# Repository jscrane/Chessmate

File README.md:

# Commodore CHESSmate

An emulation of the [Commodore CHESSmate](https://commodore.international/2022/03/26/the-history-of-the-commodore-chessmate/)
based on information from [Hans Otten](http://retro.hansotten.nl/6502-sbc/6530-6532/chessmate/).

Inspired by an article on [Hackaday](https://hackaday.com/2023/11/14/the-quaint-history-of-the-commodore-chessmate/)!

## Software

### Common
- [6502 Emulation](https://github.com/jscrane/r65emu) library
- [Arduino IDE](https://www.arduino.cc/en/software/) or [uC-Makefile](https://github.com/jscrane/uC-Makefile)

Please [configure](https://github.com/jscrane/r65emu#configuration-for-arduino) the Emulation library for your hardware.

### ESP8266
- [ESP8266 Arduino core](https://github.com/esp8266/Arduino.git)
- [TFT_eSPI](https://github.com/Bodmer/TFT_eSPI) library

Please [configure](https://github.com/Bodmer/TFT_eSPI/blob/master/User_Setup_Select.h) TFT_eSPI for your hardware.

### ESP32
- [ESP32 Arduino core](https://github.com/espressif/arduino-esp32)
- [FabGL](https://github.com/fdivitto/FabGL)

## Hardware

### Input
- a PS/2 keyboard, or
- a serial terminal, or
- hardware pushbuttons

See `config.h`.

### ESP8266
- A board, e.g., [WeMOS](https://www.wemos.cc/en/latest/d1/d1_mini.html)
- A display supported by TFT_eSPI, e.g., ILI9341

### ESP32
- A board, e.g., [LilyGO TTGO](https://www.tinytronics.nl/shop/en/development-boards/microcontroller-boards/with-wi-fi/lilygo-ttgo-vga32-esp32)
- A custom PCB with a `node32s`, see below.

## Acknowledgement

Thanks to **PCBWay** for sponsoring this lovely PCB; their service was prompt, efficient and their [KiCad plugin](https://www.pcbway.com/blog/News/PCBWay_Plug_In_for_KiCad_3ea6219c.html) made ordering painless!

- KiCad files are [here](/kicad/)
- Software for this configuration can be built (with `uC-Makefile`) as `make t=esp32`

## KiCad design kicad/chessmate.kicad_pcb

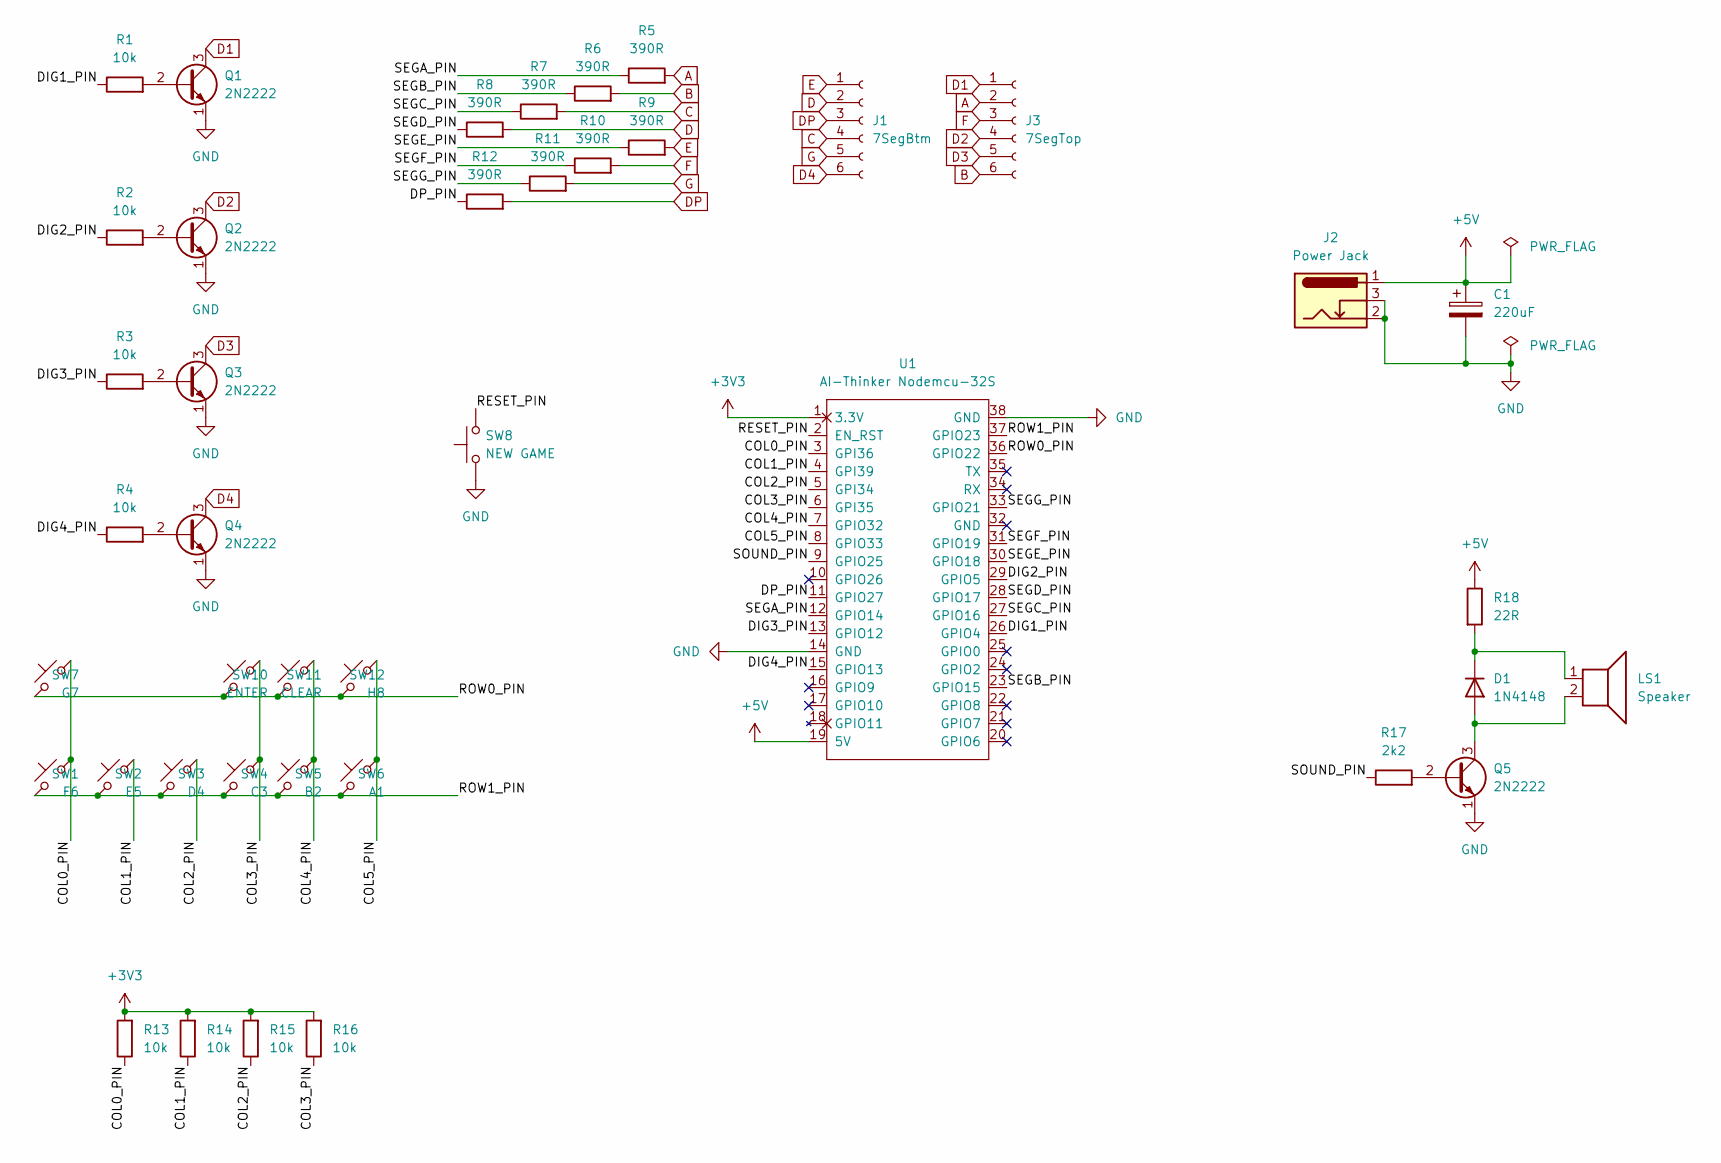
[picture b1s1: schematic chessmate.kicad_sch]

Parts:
C1: 220uF; CP_Radial_D6.3mm_P2.50mm
D1: 1N4148; D_DO-35_SOD27_P7.62mm_Horizontal
J1: 7SegBtm; PinHeader_1x06_P2.54mm_Vertical
J2: Power Jack; BarrelJack_Horizontal
J3: 7SegTop; PinHeader_1x06_P2.54mm_Vertical
LS1: Speaker; Buzzer_12x9.5RM7.0
Q1, Q2, Q3, Q4, Q5: 2N2222; TO-92_Inline
R1, R2, R3, R4: 10k; R_Axial_DIN0207_L6.3mm_D2.5mm_P2.54mm_Vertical
R5, R6, R7, R8, R9, R10, R11, R12: 390R; R_Axial_DIN0207_L6.3mm_D2.5mm_P2.54mm_Vertical
R13, R14, R15, R16: 10k; R_Axial_DIN0207_L6.3mm_D2.5mm_P7.62mm_Horizontal
R17: 2k2; R_Axial_DIN0207_L6.3mm_D2.5mm_P2.54mm_Vertical
R18: 22R; R_Axial_DIN0207_L6.3mm_D2.5mm_P2.54mm_Vertical
SW1: F6; SW_PUSH_6mm_H4.3mm
SW2: E5; SW_PUSH_6mm_H4.3mm
SW3: D4; SW_PUSH_6mm_H4.3mm
SW4: C3; SW_PUSH_6mm_H4.3mm
SW5: B2; SW_PUSH_6mm_H4.3mm
SW6: A1; SW_PUSH_6mm_H4.3mm
SW7: G7; SW_PUSH_6mm_H4.3mm
SW8: NEW GAME; SW_PUSH_6mm_H4.3mm
SW10: ENTER; SW_PUSH_6mm_H4.3mm
SW11: CLEAR; SW_PUSH_6mm_H4.3mm
SW12: H8; SW_PUSH_6mm_H4.3mm
U1: AI-Thinker Nodemcu-32S; ai-thinker nodemcu-32s

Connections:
+3V3: R13.2, R14.2, R15.2, R16.2, U1.1 (3.3V)
+5V: C1.1, J2.1, R18.1, U1.19 (5V)
/COL0_PIN: R13.1, SW1.2, SW7.2, U1.3 (GPI36)
/COL1_PIN: R14.1, SW2.2, U1.4 (GPI39)
/COL2_PIN: R15.1, SW3.2, U1.5 (GPI34)
/COL3_PIN: R16.1, SW4.2, SW10.2, U1.6 (GPI35)
/COL4_PIN: SW5.2, SW11.2, U1.7 (GPIO32)
/COL5_PIN: SW6.2, SW12.2, U1.8 (GPIO33)
/DIG1_PIN: R1.1, U1.26 (GPIO4)
/DIG2_PIN: R2.1, U1.29 (GPIO5)
/DIG3_PIN: R3.1, U1.13 (GPIO12)
/DIG4_PIN: R4.1, U1.15 (GPIO13)
/DP_PIN: R12.1, U1.11 (GPIO27)
/RESET_PIN: SW8.2, U1.2 (EN_RST)
/ROW0_PIN: SW7.1, SW10.1, SW11.1, SW12.1, U1.36 (GPIO22)
/ROW1_PIN: SW1.1, SW2.1, SW3.1, SW4.1, SW5.1, SW6.1, U1.37 (GPIO23)
/SEGA_PIN: R5.1, U1.12 (GPIO14)
/SEGB_PIN: R6.1, U1.23 (GPIO15)
/SEGC_PIN: R7.1, U1.27 (GPIO16)
/SEGD_PIN: R8.1, U1.28 (GPIO17)
/SEGE_PIN: R9.1, U1.30 (GPIO18)
/SEGF_PIN: R10.1, U1.31 (GPIO19)
/SEGG_PIN: R11.1, U1.33 (GPIO21)
/SOUND_PIN: R17.1, U1.9 (GPIO25)
A: J3.2, R5.2
B: J3.6, R6.2
C: J1.4, R7.2
D: J1.2, R8.2
D1: J3.1, Q1.3 (C)
D2: J3.4, Q2.3 (C)
D3: J3.5, Q3.3 (C)
D4: J1.6, Q4.3 (C)
DP: J1.3, R12.2
E: J1.1, R9.2
F: J3.3, R10.2
G: J1.5, R11.2
GND: C1.2, J2.2, J2.3, Q1.1 (E), Q2.1 (E), Q3.1 (E), Q4.1 (E), Q5.1 (E), SW8.1, U1.14 (GND), U1.38 (GND)
unnamed: D1.2 (A), LS1.2, Q5.3 (C)
unnamed: D1.1 (K), LS1.1, R18.2
unnamed: Q1.2 (B), R1.2
unnamed: Q2.2 (B), R2.2
unnamed: Q3.2 (B), R3.2
unnamed: Q4.2 (B), R4.2
unnamed: Q5.2 (B), R17.2

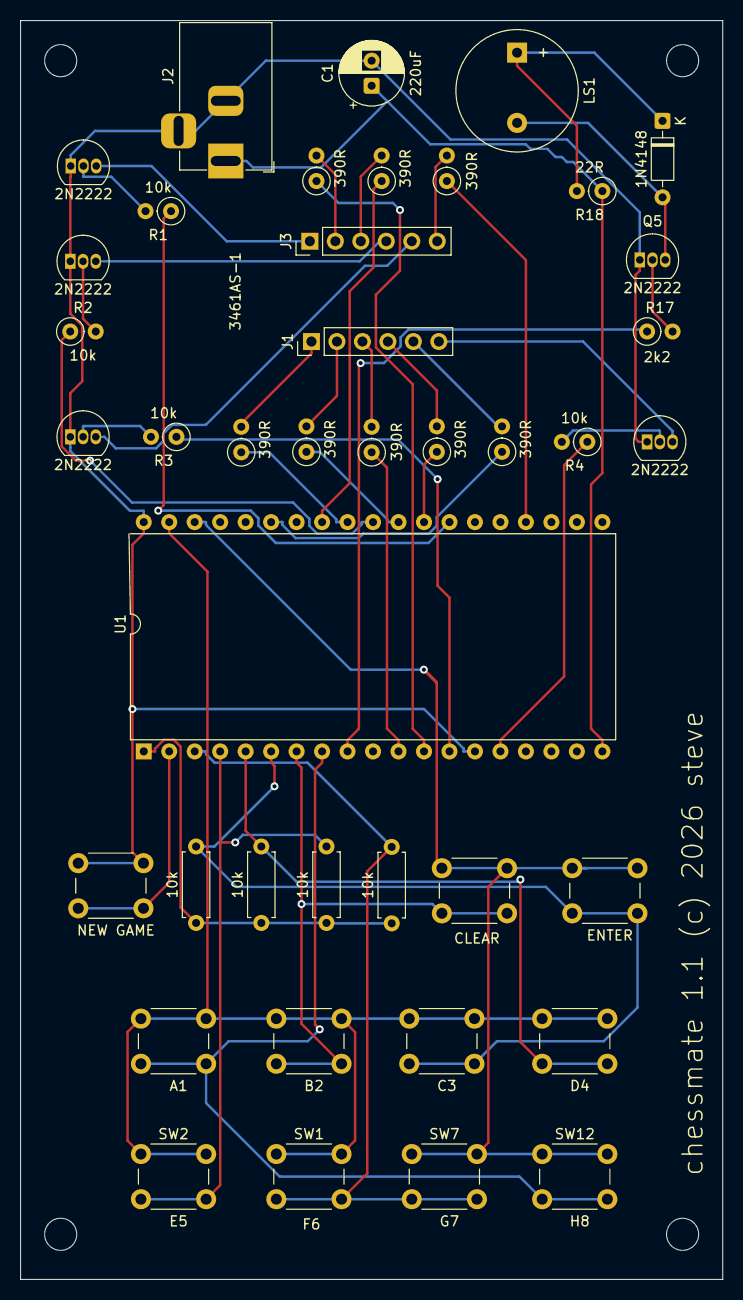
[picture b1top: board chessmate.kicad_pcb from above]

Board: 2 copper layers, 70.0 x 125.5 mm, 41 parts (0 on the bottom side), 44 nets.

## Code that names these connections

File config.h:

#pragma once

// TFT display: scr_disp
#define BG_COLOUR	BLACK
#define FG_COLOUR	RED
#define ORIENT		portrait
#define DISPLAY_X	180
#define DISPLAY_Y	200

//#define SS_DISPLAY
//#define PB_KEYPAD

// 7-segment display: ss_disp
#define DIG1_PIN	4
#define DIG2_PIN	5
#define DIG3_PIN	12
#define DIG4_PIN	13

#define SEGA_PIN	14
#define SEGB_PIN	15
#define SEGC_PIN	16
#define SEGD_PIN	17
#define SEGE_PIN	18
#define SEGF_PIN	19
#define SEGG_PIN	21
#define DP_PIN		27

// Pushbutton keypad: pb_keypad
#define ROW0_PIN	22
#define ROW1_PIN	23

// need pullup resistors on pins 34-39 on -S1 boards
#define COL0_PIN	36
#define COL1_PIN	39
#define COL2_PIN	34
#define COL3_PIN	35
#define COL4_PIN	32
#define COL5_PIN	33

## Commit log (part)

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2023-11-17 fix #2
2023-11-18 code cleanup
2023-11-18 update requirements
2023-11-18 add text
2023-11-18 more display improvements; bit-bang sound if available
2023-11-18 first attempt at timer (polling)
2023-11-18 lilygo port
2023-11-19 testing with tivac
2023-11-19 Create README.md
    notes on the timer
2024-02-23 bugfixes
2024-02-23 add openings rom
2024-02-23 Openings (#4)
    * bugfixes
    * add openings rom
2024-08-20 keyboards
2024-08-20 README.md
2024-08-21 remove setjmp
2024-08-21 hardware_run / hardware_debug_cpu()
2024-08-22 Keyboards (#5)
    * keyboards
    * README.md
    * remove setjmp
    * hardware_run / hardware_debug_cpu()
2024-09-22 fix breakages
2024-11-05 infrastructure for 7-segment display abstraction
2024-11-05 skeleton for hardware keypad
2024-11-12 refactoring
2024-11-12 cleanup
2024-11-12 refactoring (#8)
    * refactoring
    * cleanup
2024-11-12 refactor for hardware keypad
2024-11-12 cleanups
2024-11-12 more cleanups
2024-11-12 hardware implementation
2024-11-12 remove hardware pin for led4
2024-11-14 minor updates
2024-11-16 simpletimer
2024-11-21 7-segment display pin assignment
2024-11-21 -DUSE_OWN_DISPLAY
2024-11-21 bugofx
2024-11-22 use DP for LEDs
2024-11-22 refactor RIOT
2024-11-23 working keypad
2024-11-23 Hardware implementation (#9)
    * infrastructure for 7-segment display abstraction
    * skeleton for hardware keypad
    * bugfixes
    * refactor for hardware keypad
    * cleanups
    * more cleanups
2024-11-24 schematic diagram
2025-08-26 add schematic + layout
2025-08-26 remove .prl
2026-01-23 kicad updates
2026-01-24 new machine APIs
2026-01-24 KiCAD (#11)
    * schematic diagram
    * add schematic + layout
    * ...
    * remove .prl
    * kicad updates
2026-02-06 updates for lib v1.2.0
2026-02-16 remove tivac and FabGL
2026-02-16 update for esp8266
2026-02-20 updates for new Display
2026-02-23 speedups for esp8bit
2026-02-23 adding bom
2026-02-24 replace 7-seg footprint with pin headers
2026-02-24 update nodemcu footprint
2026-02-24 move component values and switch names to F.Silkscreen layer
2026-02-24 routing
2026-02-24 add ground plane
2026-02-24 add mounting holes
2026-02-25 Address v1.0 PCB errors (#13)
    * replace 7-seg footprint with pin headers
    * update nodemcu footprint
    * move component values and switch names to F.Silkscreen layer
    * routing
    * add ground plane
    * add mounting holes
2026-03-10 RIOT is now a Memory::Device again
2026-03-27 update cpu debugging
2026-04-09 adding pic
2026-04-09 14 pcbway (#15)
2026-04-13 Fix links and enhance PCBWay acknowledgment
    Updated links and improved acknowledgment wording.

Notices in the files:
kicad/chessmate.kicad_pcb:
chessmate 1.1 (c) 2026 steve
